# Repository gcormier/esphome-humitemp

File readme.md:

# esphome-humitemp
- SHT3x temperature/humidity sensor
- ESP32-C3
- NEW: Native USB-C programming support (hold button 1st time)
- Or, backup/legacy programming header for [eflashy32](https://github.com/gcormier/eflashy32)
- Powered by 5V USB
- Designed for `esphome` but can be flashed with anything you want

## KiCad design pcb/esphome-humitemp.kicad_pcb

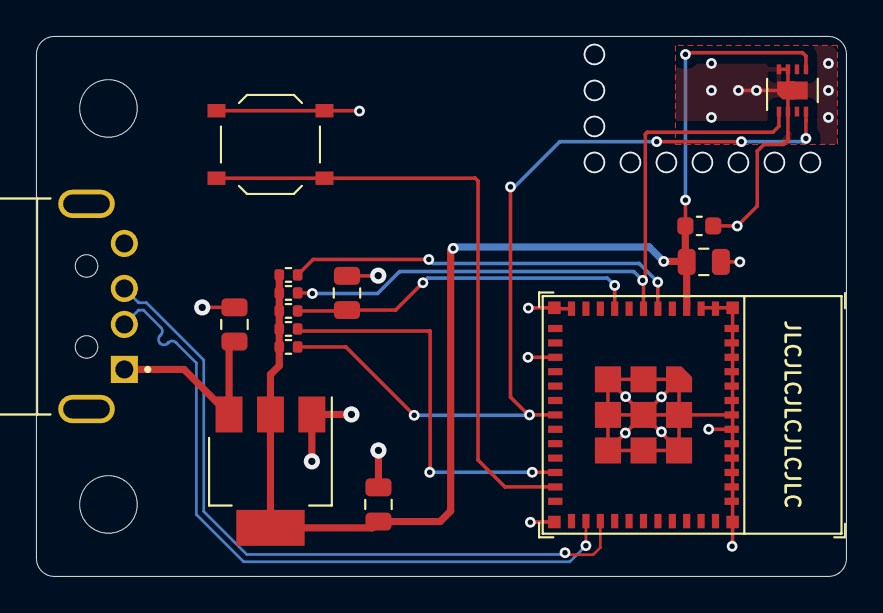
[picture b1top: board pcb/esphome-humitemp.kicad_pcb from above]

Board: 2 copper layers, 45.0 x 30.0 mm, 17 parts (0 on the bottom side), 11 nets.

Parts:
C1, C2: 1uF; C_0805_2012Metric
C4, C6: 10u; C_0805_2012Metric
C5: 0.1u; C_0603_1608Metric
H1, H2: MountingHole; MountingHole_3.2mm_M3
J2: USB_IN; MOLEX_48037-0001
R2, R3, R4, R5, R6: 10k; R_0402_1005Metric
SW1: RESET; SW_Push_1P1T_XKB_TS-1187A
U1: SHT3x; Sensirion_DFN-8-1EP_2.5x2.5mm_P0.5mm_EP1.1x1.7mm
U3: AMS1117-3.3; SOT-223-3_TabPin2
U4: ESP32-C3-MINI-1

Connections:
+3V3: C2.1, C5.2, C6.2, R2.1, R3.1, R4.1, R5.1, R6.1, U1.5 (VDD), U3.2 (VO), U4.3 (3V3)
/EN: C4.2, R4.2, U4.8 (EN/CHIP_PU)
/GPIO0: SW1.1 (A), U4.23 (GPIO9)
D+: J2.3 (D+), U4.27 (GPIO19/USB_D+)
D-: J2.2 (D-), U4.26 (GPIO18/USB_D-)
GND: C1.2, C2.2, C4.1, C5.1, C6.1, J2.4 (GND), SW1.2 (B), U1.2 (ADDR), U1.7 (R), U1.8 (VSS), U1.9 (VSS), U3.1 (GND), U4.1 (GND), U4.2 (GND), U4.11 (GND), U4.14 (GND), U4.36 (GND), U4.37 (GND), U4.38 (GND), U4.39 (GND), U4.40 (GND), U4.41 (GND), U4.42 (GND), U4.43 (GND), U4.44 (GND), U4.45 (GND), U4.46 (GND), U4.47 (GND), U4.48 (GND), U4.49 (GND), U4.50 (GND), U4.51 (GND), U4.52 (GND), U4.53 (GND)
unnamed: R5.2, U4.5 (GPIO2/ADC1_CH2)
unnamed: R6.2, U4.22 (GPIO8)
SCL: R3.2, U1.4 (SCL), U4.18 (GPIO4/ADC1_CH4)
SDA: R2.2, U1.1 (SDA), U4.6 (GPIO3/ADC1_CH3)
VBUS: C1.1, J2.1 (VBUS), U3.3 (VI)

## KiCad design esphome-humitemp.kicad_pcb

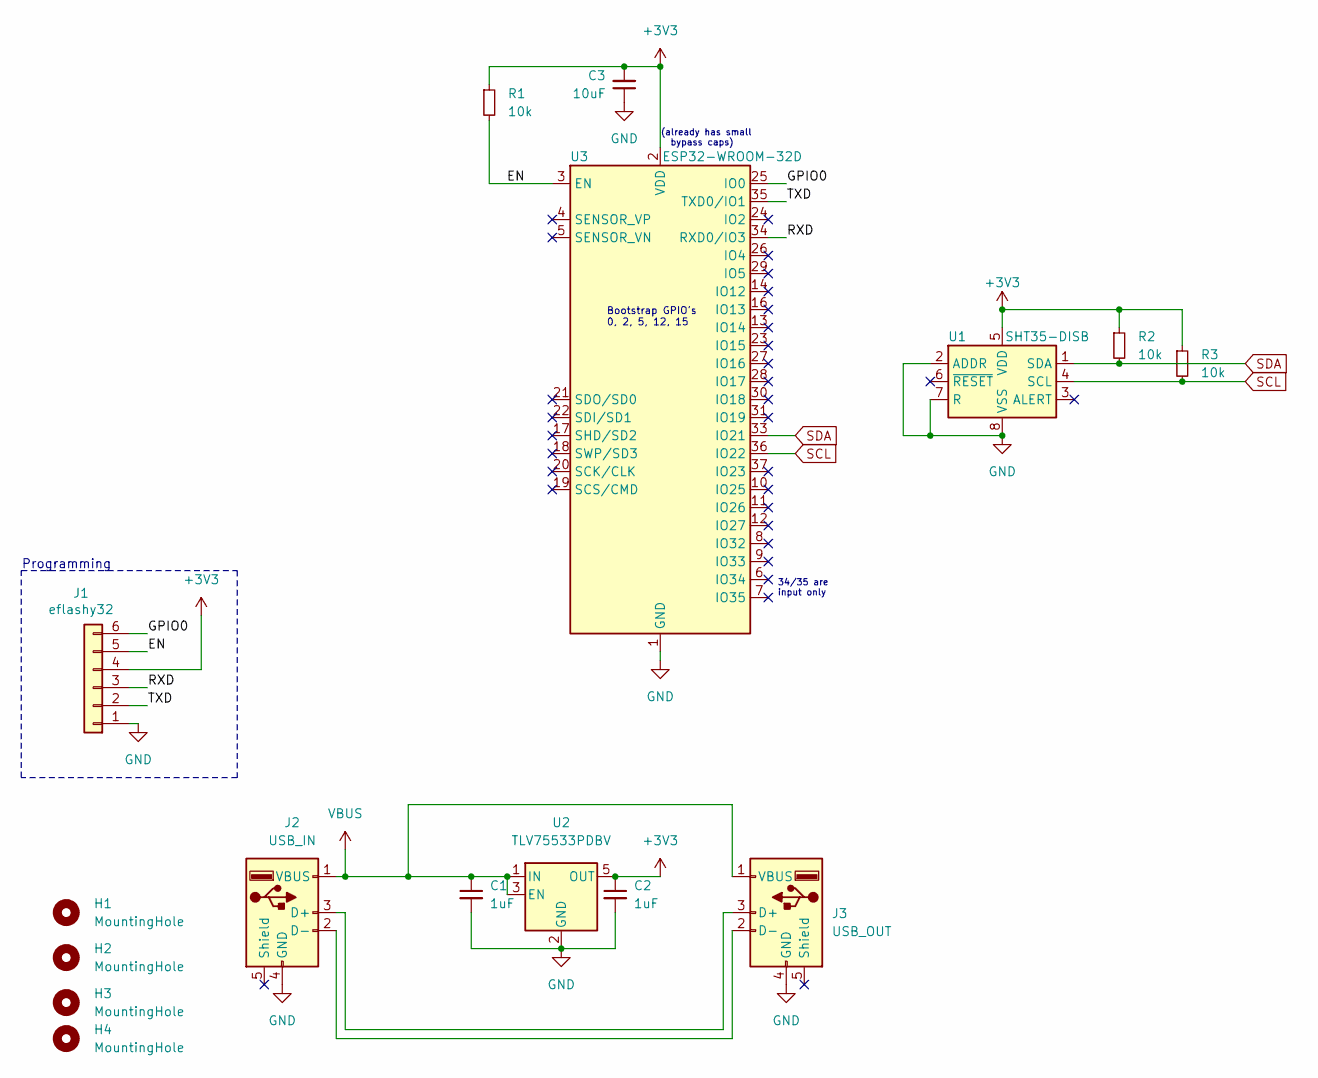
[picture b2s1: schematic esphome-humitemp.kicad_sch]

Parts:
C1, C2: 1uF; C_0805_2012Metric; LCSC C28323
C3: 10uF; C_0805_2012Metric; LCSC C15850
H1, H2, H3, H4: MountingHole; MountingHole_3.2mm_M3
J1: eflashy32; PinHeader_1x06_P2.54mm_Vertical
J2: USB_IN; MOLEX_48037-0001; LCSC C112454
J3: USB_OUT; USB_A_Molex_67643_Horizontal; LCSC C2346
R1, R2, R3: 10k; R_0805_2012Metric; LCSC C17414
U1: SHT35-DISB; Sensirion_DFN-8-1EP_2.5x2.5mm_P0.5mm_EP1.1x1.7mm; LCSC C90161
U2: TLV75533PDBV; SOT-23-5; LCSC C404027
U3: ESP32-WROOM-32D; ESP32-WROOM-32; LCSC C473012

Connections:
+3V3: C2.1, C3.2, J1.4, R1.1, R2.1, R3.1, U1.5 (VDD), U2.5 (OUT), U3.2 (VDD)
/EN: J1.5, R1.2, U3.3 (EN)
/GPIO0: J1.6, U3.25 (IO0)
/RXD: J1.3, U3.34 (RXD0/IO3)
/TXD: J1.2, U3.35 (TXD0/IO1)
GND: C1.2, C2.2, C3.1, J1.1, J2.4 (GND), J3.4 (GND), U1.2 (ADDR), U1.7 (R), U1.8 (VSS), U1.9 (VSS), U2.2 (GND), U3.1 (GND), U3.15 (GND), U3.38 (GND), U3.39 (GND)
unnamed: J2.2 (D-), J3.2 (D-)
unnamed: J2.3 (D+), J3.3 (D+)
SCL: R3.2, U1.4 (SCL), U3.36 (IO22)
SDA: R2.2, U1.1 (SDA), U3.33 (IO21)
VBUS: C1.1, J2.1 (VBUS), J3.1 (VBUS), U2.1 (IN), U2.3 (EN)

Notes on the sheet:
Programming
Bootstrap GPIO's 0, 2, 5, 12, 15
(already has small bypass caps)
34/35 are input only

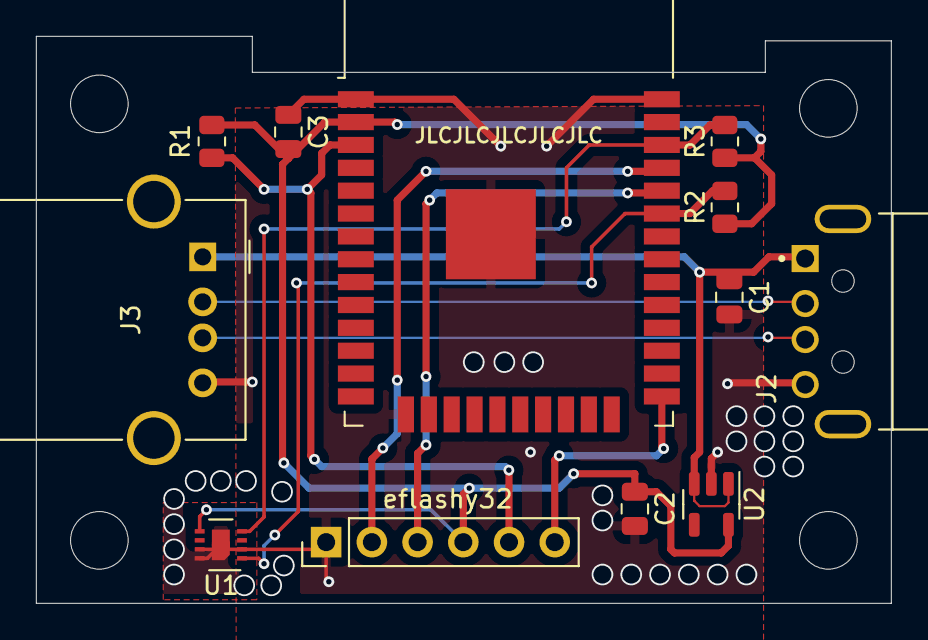
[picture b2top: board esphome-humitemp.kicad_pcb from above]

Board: 2 copper layers, 47.5 x 31.5 mm, 16 parts (0 on the bottom side), 11 nets.

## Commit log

2021-08-26 pics
2021-08-26 pic2
2021-08-26 move thermal via slightly to avoid bad programmer placement
2021-08-26 esphome yaml file
2023-09-19 v2 ecad
2023-09-19 actions
2023-09-19 yamls
2023-09-19 reorg
2023-09-19 fix a few issues
2023-09-19 add model
2023-09-19 ignore lock files
2023-09-24 disable download
2023-09-24 reenable download
2023-09-28 final tweaks
2023-09-28 panel size
2023-09-28 minsize
2023-09-28 try more
2023-09-28 rounded edges
2023-09-28 add another tab
2023-09-28 rotate and send it
2023-09-28 edgecuts for vscoer
2023-09-28 rerender v2
2023-09-28 docs
2023-09-30 fix part number for 10k
2023-10-01 tindie badget
2023-10-17 ignore secrets
2023-10-17 esphome ignore
2023-10-17 c3 updates
2023-12-21 test
2023-12-21 consol
2023-12-21 cache
2023-12-21 testcache
2023-12-21 rename
2023-12-21 tmate
2023-12-21 subf
2023-12-21 nuttin
2023-12-21 after
2023-12-22 button wakeup
2023-12-22 pullup
2023-12-22 back
